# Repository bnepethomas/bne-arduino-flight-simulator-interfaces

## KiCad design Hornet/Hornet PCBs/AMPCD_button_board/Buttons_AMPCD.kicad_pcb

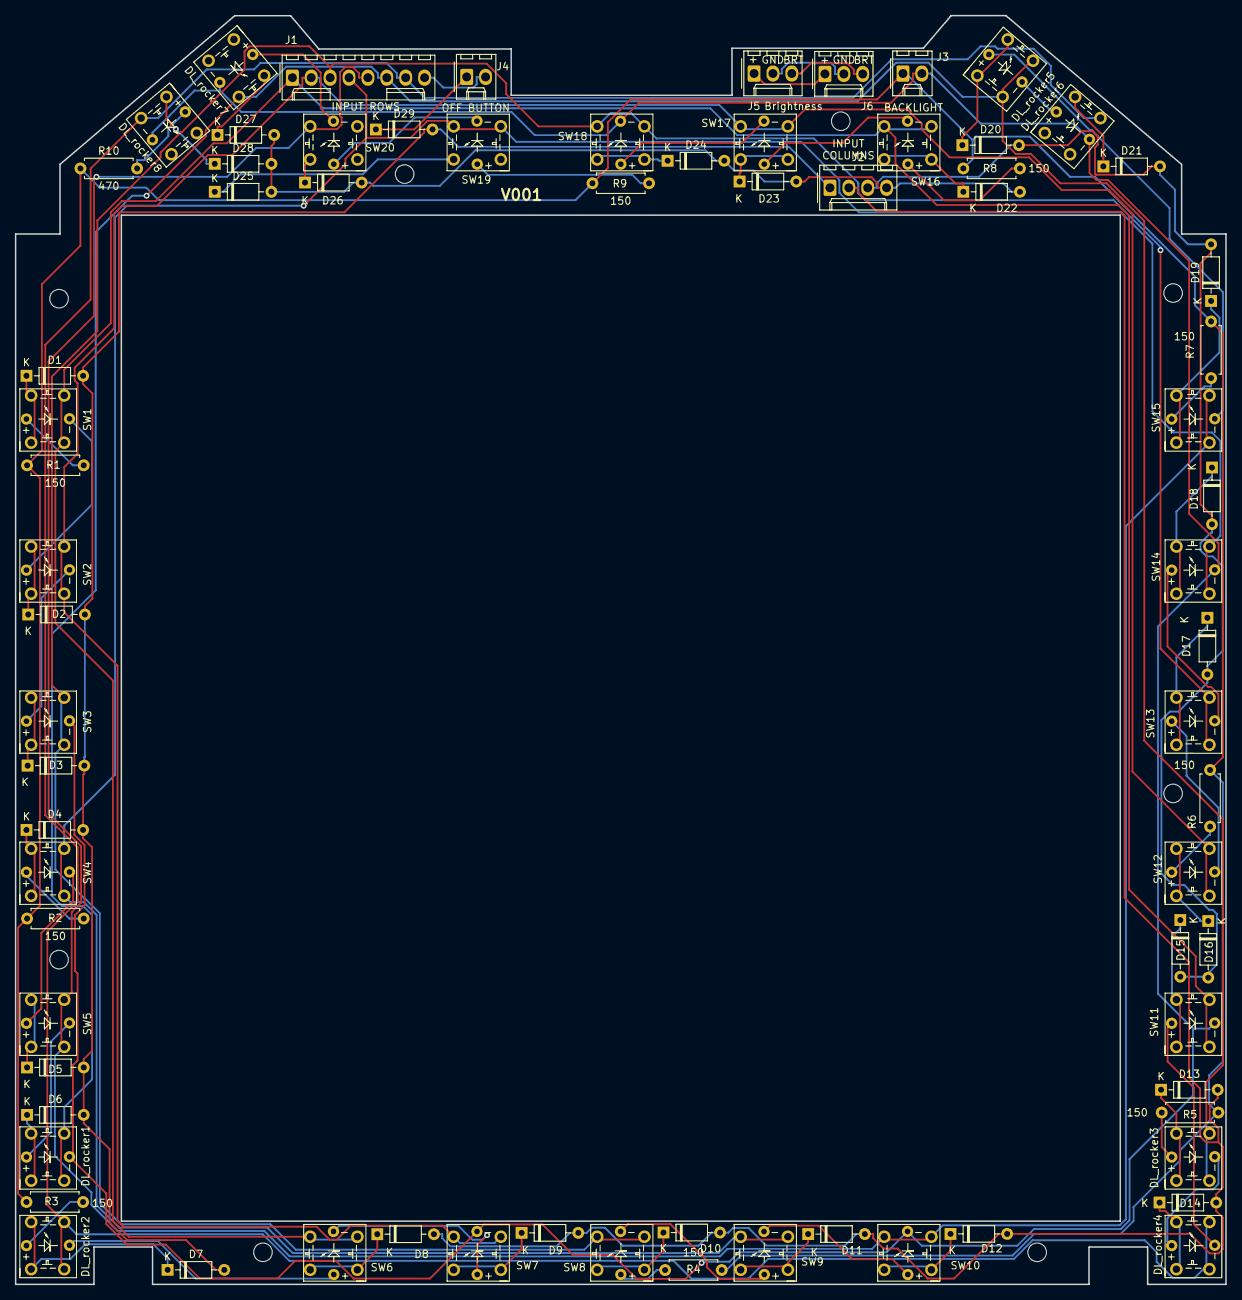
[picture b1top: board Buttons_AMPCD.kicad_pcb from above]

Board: 2 copper layers, 162.8 x 170.7 mm, 81 parts (0 on the bottom side), 74 nets.

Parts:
D1, D2, D3, D4, D5, D6, D7, D8, D9, D10, D11, D12, D13, D14, D15, D16, D17, D18, D19, D20, D21, D22, D23, D24, D25, D26, D27, D28, D29: 1N4148; D_DO-35_SOD27_P7.62mm_Horizontal
DL_rocker1, DL_rocker2, DL_rocker3, DL_rocker4, DL_rocker5, DL_rocker6, DL_rocker7, DL_rocker8: SW_Push; PT_Small_Tactile_Switch_With_LED
H1, H2, H3, H4, H5, H6, H7, H8: MountingHole; MountingHole_2.5mm
J1: Conn_01x08_Female; Molex_1x08_P2.54mm_Vertical
J2: Conn_01x04_Female; Molex_1x04_P2.54mm_Vertical
J3, J4: Conn_01x02_Female; Molex_1x02_P2.54mm_Vertical
J5, J6: Conn_01x03_Female; Molex_1x03_P2.54mm_Vertical
R1, R2, R3, R4, R5, R6, R7, R8, R9: 150; R_Axial_DIN0207_L6.3mm_D2.5mm_P7.62mm_Horizontal
R10: 470; R_Axial_DIN0207_L6.3mm_D2.5mm_P7.62mm_Horizontal
SW1, SW2, SW3, SW4, SW5, SW6, SW7, SW8, SW9, SW10, SW11, SW12, SW13, SW14, SW15, SW16, SW17, SW18, SW19, SW20: SW_Push; PT_Small_Tactile_Switch_With_LED

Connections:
/Backlight+12V: J3.1, R1.1, R2.1, R3.1, R4.1, R5.1, R6.1, R7.1, R8.1, R9.1, R10.1
/Col0: D1.2, D2.2, D3.2, D4.2, D5.2, D6.2, D7.2, D29.2, J2.1
/Col1: D8.2, D9.2, D10.2, D11.2, D12.2, D13.2, D14.2, J2.2
/Col2: D15.2, D16.2, D17.2, D18.2, D19.2, D20.2, D21.2, J2.3
/Col3: D22.2, D23.2, D24.2, D25.2, D26.2, D27.2, D28.2, J2.4
/Row0: J1.1, SW1.3, SW1.4, SW6.3, SW6.4, SW11.3, SW11.4, SW16.3, SW16.4
/Row1: J1.2, SW2.3, SW2.4, SW7.3, SW7.4, SW12.3, SW12.4, SW17.3, SW17.4
/Row2: J1.3, SW3.3, SW3.4, SW8.3, SW8.4, SW13.3, SW13.4, SW18.3, SW18.4
/Row3: J1.4, SW4.3, SW4.4, SW9.3, SW9.4, SW14.3, SW14.4, SW19.3, SW19.4
/Row4: J1.5, SW5.3, SW5.4, SW10.3, SW10.4, SW15.3, SW15.4, SW20.4
/Row5: DL_rocker1.3, DL_rocker1.4, DL_rocker3.3, DL_rocker3.4, DL_rocker5.3, DL_rocker5.4, DL_rocker7.4, J1.6
/Row6: DL_rocker2.3, DL_rocker2.4, DL_rocker4.3, DL_rocker4.4, DL_rocker6.4, DL_rocker8.3, J1.7
/Row7: J1.8, J4.2
GND: DL_rocker1.6, DL_rocker6.6, DL_rocker7.6, DL_rocker8.6, J3.2, SW3.6, SW7.6, SW10.6, SW11.6, SW14.6, SW18.6
unnamed: D1.1, SW1.1, SW1.2
unnamed: D2.1, SW2.1, SW2.2
unnamed: D3.1, SW3.1, SW3.2
unnamed: D4.1, SW4.1, SW4.2
unnamed: D5.1, SW5.1, SW5.2
unnamed: D6.1, DL_rocker1.1, DL_rocker1.2
unnamed: D7.1, DL_rocker2.1, DL_rocker2.2
unnamed: D8.1, SW6.1, SW6.2
unnamed: D9.1, SW7.1, SW7.2
unnamed: D10.1, SW8.1, SW8.2
unnamed: D11.1, SW9.1, SW9.2
unnamed: D12.1, SW10.1, SW10.2
unnamed: D13.1, DL_rocker3.1, DL_rocker3.2
unnamed: D14.1, DL_rocker4.1, DL_rocker4.2
unnamed: D15.1, SW11.1, SW11.2
unnamed: D16.1, SW12.1, SW12.2
unnamed: D17.1, SW13.1, SW13.2
unnamed: D18.1, SW14.1, SW14.2
unnamed: D19.1, SW15.1, SW15.2
unnamed: D20.1, DL_rocker5.1, DL_rocker5.2
unnamed: D21.1, DL_rocker6.2
unnamed: D22.1, SW16.1, SW16.2
unnamed: D23.1, SW17.1, SW17.2
unnamed: D24.1, SW18.1, SW18.2
unnamed: D25.1, SW19.2
unnamed: D26.1, SW20.2
unnamed: D27.1, DL_rocker7.2
unnamed: D28.1, DL_rocker8.1
unnamed: D29.1, J4.1
unnamed: DL_rocker1.5, SW5.6
unnamed: DL_rocker2.5, R3.2
unnamed: DL_rocker2.6, SW6.5
unnamed: DL_rocker3.5, R5.2
unnamed: DL_rocker3.6, DL_rocker4.5
unnamed: DL_rocker4.6, SW11.5
unnamed: DL_rocker5.5, SW15.6
unnamed: DL_rocker5.6, DL_rocker6.5
unnamed: DL_rocker7.5, SW20.6
unnamed: DL_rocker8.5, R10.2
unnamed: J5.1, J6.1
unnamed: J5.2, J6.2
unnamed: J5.3, J6.3
unnamed: R1.2, SW1.5
unnamed: R2.2, SW4.5
unnamed: R4.2, SW8.5
unnamed: R6.2, SW12.5
unnamed: R7.2, SW15.5
unnamed: R8.2, SW16.5
unnamed: R9.2, SW19.5
unnamed: SW1.6, SW2.5
unnamed: SW2.6, SW3.5
unnamed: SW4.6, SW5.5
unnamed: SW6.6, SW7.5
unnamed: SW8.6, SW9.5
unnamed: SW9.6, SW10.5
unnamed: SW12.6, SW13.5
unnamed: SW13.6, SW14.5
unnamed: SW16.6, SW17.5
unnamed: SW17.6, SW18.5
unnamed: SW19.6, SW20.5

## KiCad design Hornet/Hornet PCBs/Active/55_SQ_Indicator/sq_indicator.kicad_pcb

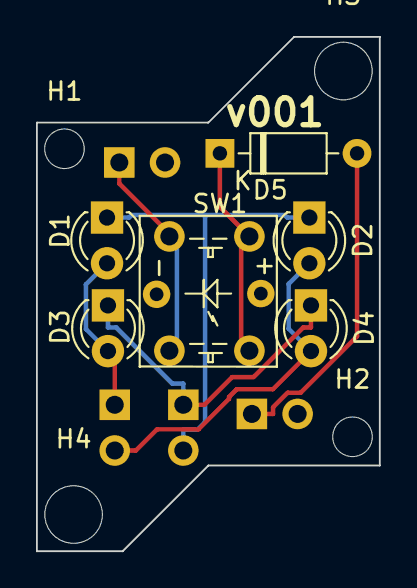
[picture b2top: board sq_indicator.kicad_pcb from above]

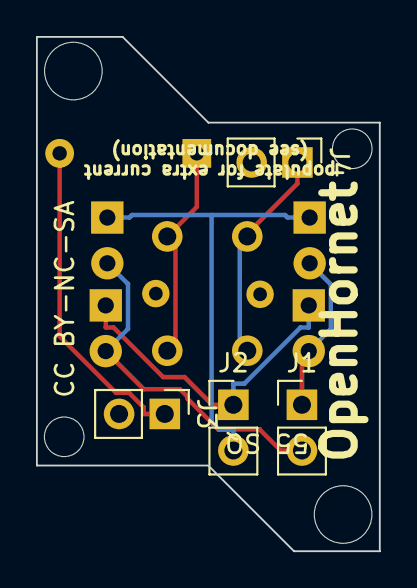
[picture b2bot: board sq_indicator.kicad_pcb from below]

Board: 2 copper layers, 19.1 x 28.6 mm, 14 parts (4 on the bottom side), 7 nets.

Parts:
D1, D2, D3, D4: LED; LED_D3.0mm
D5: 1N4148; D_DO-35_SOD27_P7.62mm_Horizontal
H1, H2: MountingHole; MountingHole_2.2mm_M2
H3, H4: MountingHole; MountingHole_3.2mm_M3
J1: LedAnode; PinHeader_1x02_P2.54mm_Vertical
J2: LedCathode; PinHeader_1x02_P2.54mm_Vertical
J3: SwitchCol; PinHeader_1x02_P2.54mm_Vertical
J4: SwitchRow; PinHeader_1x02_P2.54mm_Vertical
SW1: push; PT_Small_Tactile_Switch_With_LED

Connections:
unnamed: D1.1, D2.1, J2.2
unnamed: D1.2, D3.2, J1.1
unnamed: D2.2, D4.2, J1.2
unnamed: D3.1, D4.1, J2.1
unnamed: D5.1, SW1.1, SW1.2
unnamed: D5.2, J3.1
unnamed: J4.1, SW1.3, SW1.4

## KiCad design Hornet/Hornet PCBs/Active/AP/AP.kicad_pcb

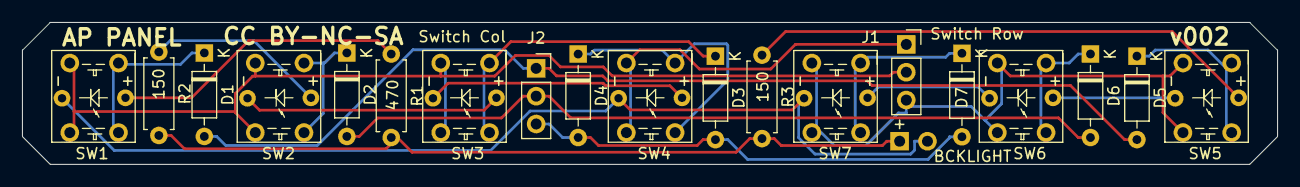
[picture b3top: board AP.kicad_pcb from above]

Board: 2 copper layers, 114.6 x 13.0 mm, 20 parts (1 on the bottom side), 22 nets.

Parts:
D1, D2, D3, D4, D5, D6, D7: D; D_Signal_P7.62mm_Horizontal
J1: ROWS; PinSocket_1x03_P2.54mm_Vertical
J2: COLS; PinSocket_1x03_P2.54mm_Vertical
J3: Conn_01x02_Female; PinSocket_1x02_P2.54mm_Vertical
R1: 470; R_Axial_DIN0207_L6.3mm_D2.5mm_P7.62mm_Horizontal
R2, R3: 150; R_Axial_DIN0207_L6.3mm_D2.5mm_P7.62mm_Horizontal
SW1, SW2, SW3, SW4, SW5, SW6, SW7: SW_SPST; PT_Small_Tactile_Switch_With_LED

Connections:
/+BCKLGT: J3.1, R1.2, R2.2, R3.2
/-BCKLGT: J3.2, SW1.6, SW4.6, SW7.6
/COL8: D1.2, D5.2, J2.1
/COL9: D2.2, D6.2, J2.2
/COL10: D3.2, D4.2, D7.2, J2.3
/ROW2: J1.1, SW4.3, SW4.4
/ROW5: J1.2, SW1.3, SW1.4, SW2.3, SW2.4, SW3.3, SW3.4
/ROW6: J1.3, SW5.3, SW5.4, SW6.3, SW6.4, SW7.3, SW7.4
unnamed: D1.1, SW1.1, SW1.2
unnamed: D2.1, SW2.1, SW2.2
unnamed: D3.1, SW3.1, SW3.2
unnamed: D4.1, SW4.1, SW4.2
unnamed: D5.1, SW5.1, SW5.2
unnamed: D6.1, SW6.1, SW6.2
unnamed: D7.1, SW7.1, SW7.2
unnamed: R1.1, SW1.5
unnamed: R2.1, SW2.5
unnamed: R3.1, SW5.5
unnamed: SW2.6, SW3.5
unnamed: SW3.6, SW4.5
unnamed: SW5.6, SW6.5
unnamed: SW6.6, SW7.5

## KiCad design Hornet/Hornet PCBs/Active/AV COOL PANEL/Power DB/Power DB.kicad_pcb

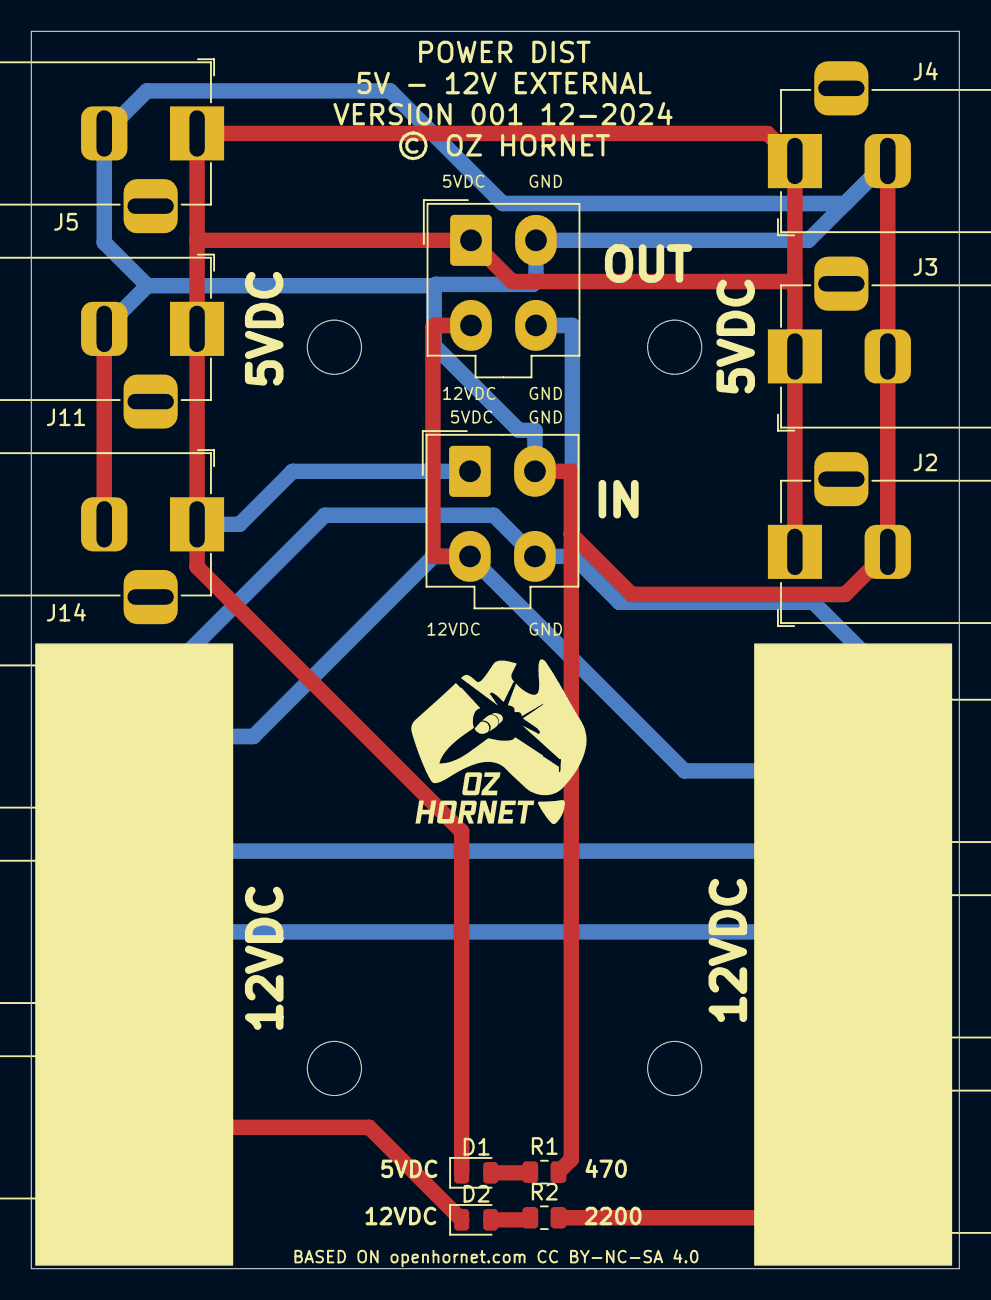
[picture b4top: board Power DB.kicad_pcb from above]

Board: 2 copper layers, 60.0 x 80.0 mm, 18 parts (0 on the bottom side), 6 nets.

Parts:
D1, D2: LED; LED_0805_2012Metric
J1, J10: Mini-Fit Jr. 2x02; Molex_Mini-Fit_Jr_5566-04A_2x02_P4.20mm_Vertical
J2, J3, J4, J5, J6, J7, J8, J9, J11, J12, J13, J14: Conn_01x02_Socket; BarrelJack_Horizontal
R1, R2: R; R_0805_2012Metric

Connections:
/5VDC: D1.1 (K), J1.1, J2.1, J3.1, J4.1, J5.1, J10.1, J11.1, J14.1
/5VGND: J1.2 (Pin_3), J2.2, J3.2, J4.2, J5.2, J10.2 (Pin_3), J11.2, J14.2, R1.2
/12VDC: D2.1 (K), J1.3 (Pin_2), J6.1, J7.1, J8.1, J9.1, J10.3 (Pin_2), J12.1, J13.1
/12VGND: J1.4, J6.2, J7.2, J8.2, J9.2, J10.4, J12.2, J13.2, R2.2
unnamed: D1.2 (A), R1.1
unnamed: D2.2 (A), R2.1

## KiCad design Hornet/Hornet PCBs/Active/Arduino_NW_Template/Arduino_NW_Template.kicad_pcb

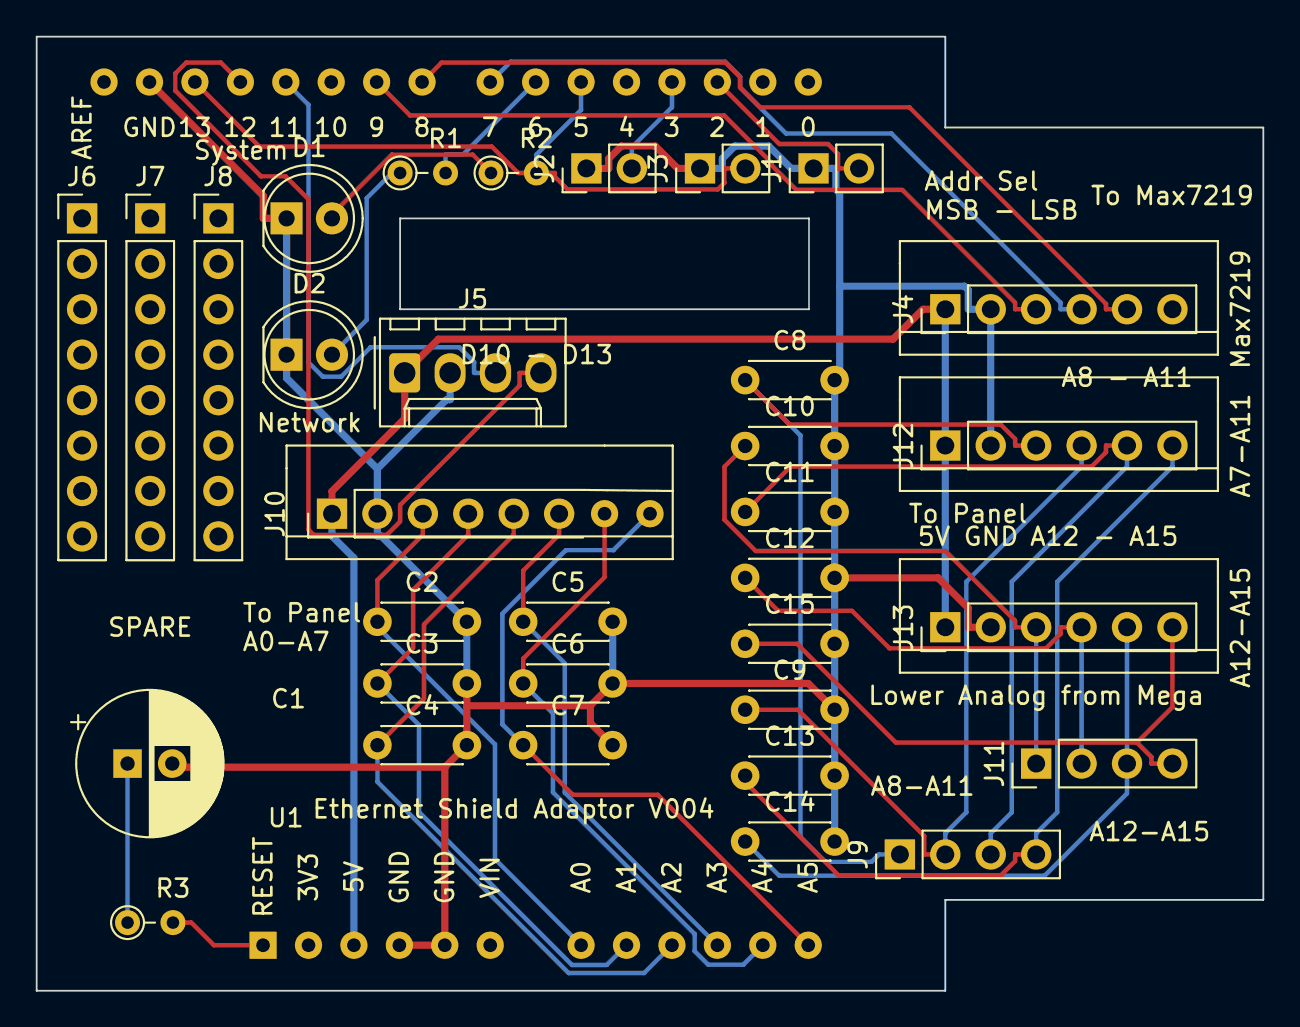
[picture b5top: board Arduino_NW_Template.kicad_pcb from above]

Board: 2 copper layers, 68.6 x 53.3 mm, 34 parts (0 on the bottom side), 29 nets.

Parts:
C1: 47uF; PT_CP_Radial_D8.0mm_P2.50mm
C2, C3, C4, C5, C6, C7, C8, C9, C10, C11, C12, C13, C14, C15: 0.1uF; C_Disc_D4.3mm_W1.9mm_P5.00mm
D1: Green; LED_D5.0mm
D2: Red; LED_D5.0mm
J1, J2, J3: Conn_01x02_Female; PinHeader_1x02_P2.54mm_Vertical
J4, J12, J13: PT_Conn_01x06; PT_PinHeader_1x06_P2.54mm_Vertical
J5: PT_Conn_01x06; Molex_1x04_P2.54mm_Vertical
J6, J7, J8: Conn_01x08_Female; PinHeader_1x08_P2.54mm_Vertical
J9, J11: Conn_01x04_Female; PinHeader_1x04_P2.54mm_Vertical
J10: Conn_01x08_Female; PT_PinHeader_1x08_P2.54mm_Vertical
R1, R2: 330; PT_R_Axial_DIN0204_L3.6mm_D1.6mm_P2.54mm_Vertical
R3: 500; PT_R_Axial_DIN0204_L3.6mm_D1.6mm_P2.54mm_Vertical
U1: PT_Ethernet_Shield; PT_Ethernet_Shield_v001

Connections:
+5V: J4.1, J5.1, J10.1, J12.1, J13.1, U1.3
GND: C1.2, C2.2, C3.2, C4.2, C5.2, C6.2, C7.2, C8.2, C9.2, C10.2, C11.2, C12.2, C13.2, C14.2, C15.2, D1.1, D2.1, J1.1, J2.1, J3.1, J4.2, J5.2, J10.2, J12.2, J13.2, U1.4, U1.5, U1.27
unnamed: C1.1, R3.1
unnamed: C2.1, J10.3, U1.7
unnamed: C3.1, J10.4, U1.8
unnamed: C4.1, J10.5, U1.9
unnamed: C5.1, J10.6, U1.10
unnamed: C6.1, J10.7, U1.11
unnamed: C7.1, J10.8, U1.12
unnamed: C8.1, J9.1, J12.3
unnamed: C9.1, J9.2, J12.4
unnamed: C10.1, J11.1, J13.3
unnamed: C11.1, J9.3, J12.5
unnamed: C12.1, J11.2, J13.4
unnamed: C13.1, J9.4, J12.6
unnamed: C14.1, J11.3, J13.5
unnamed: C15.1, J11.4, J13.6
unnamed: D1.2, R2.1
unnamed: D2.2, R1.1
unnamed: J1.2, U1.15
unnamed: J2.2, U1.16
unnamed: J3.2, R2.2, U1.18, U1.26
unnamed: J4.3, U1.22
unnamed: J4.4, U1.20
unnamed: J4.5, U1.21
unnamed: J5.3, U1.24
unnamed: J5.4, U1.25
unnamed: R1.2, U1.19
unnamed: R3.2, U1.1

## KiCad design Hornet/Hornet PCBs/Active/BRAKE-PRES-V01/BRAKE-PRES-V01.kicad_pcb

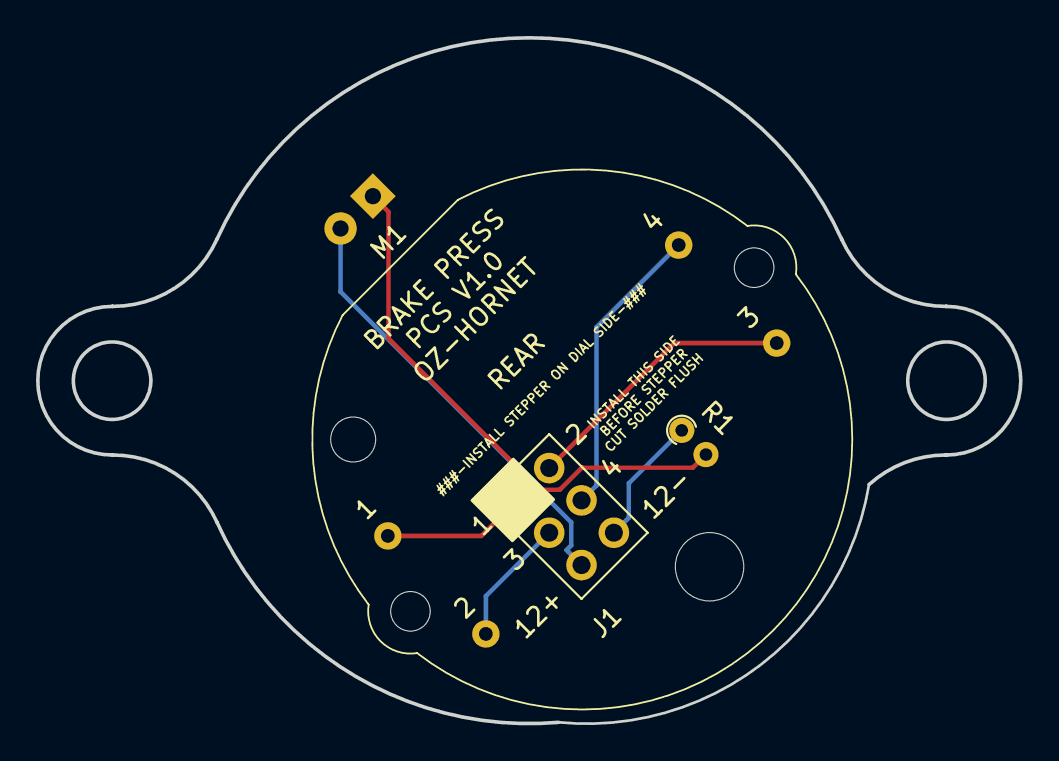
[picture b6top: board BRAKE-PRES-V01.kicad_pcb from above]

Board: 2 copper layers, 54.6 x 38.1 mm, 4 parts (1 on the bottom side), 7 nets.

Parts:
D1: LED; LED_D3.0mm_Clear
J1: Conn_02x03_Odd_Even; PinHeader_2x03_P2.54mm_Vertical
M1: Stepper_Motor_bipolar; VID29-02
R1: R; R_Axial_DIN0204_L3.6mm_D1.6mm_P1.90mm_Vertical

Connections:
/LED+12V: D1.2 (A), J1.5
/LED-12V: J1.6, R1.1
/STEPPER-1-1: J1.1, M1.1
/STEPPER-1-2: J1.3, M1.2 (-)
/STEPPER-1-3: J1.2, M1.3
/STEPPER-1-4: J1.4, M1.4
unnamed: D1.1 (K), R1.2

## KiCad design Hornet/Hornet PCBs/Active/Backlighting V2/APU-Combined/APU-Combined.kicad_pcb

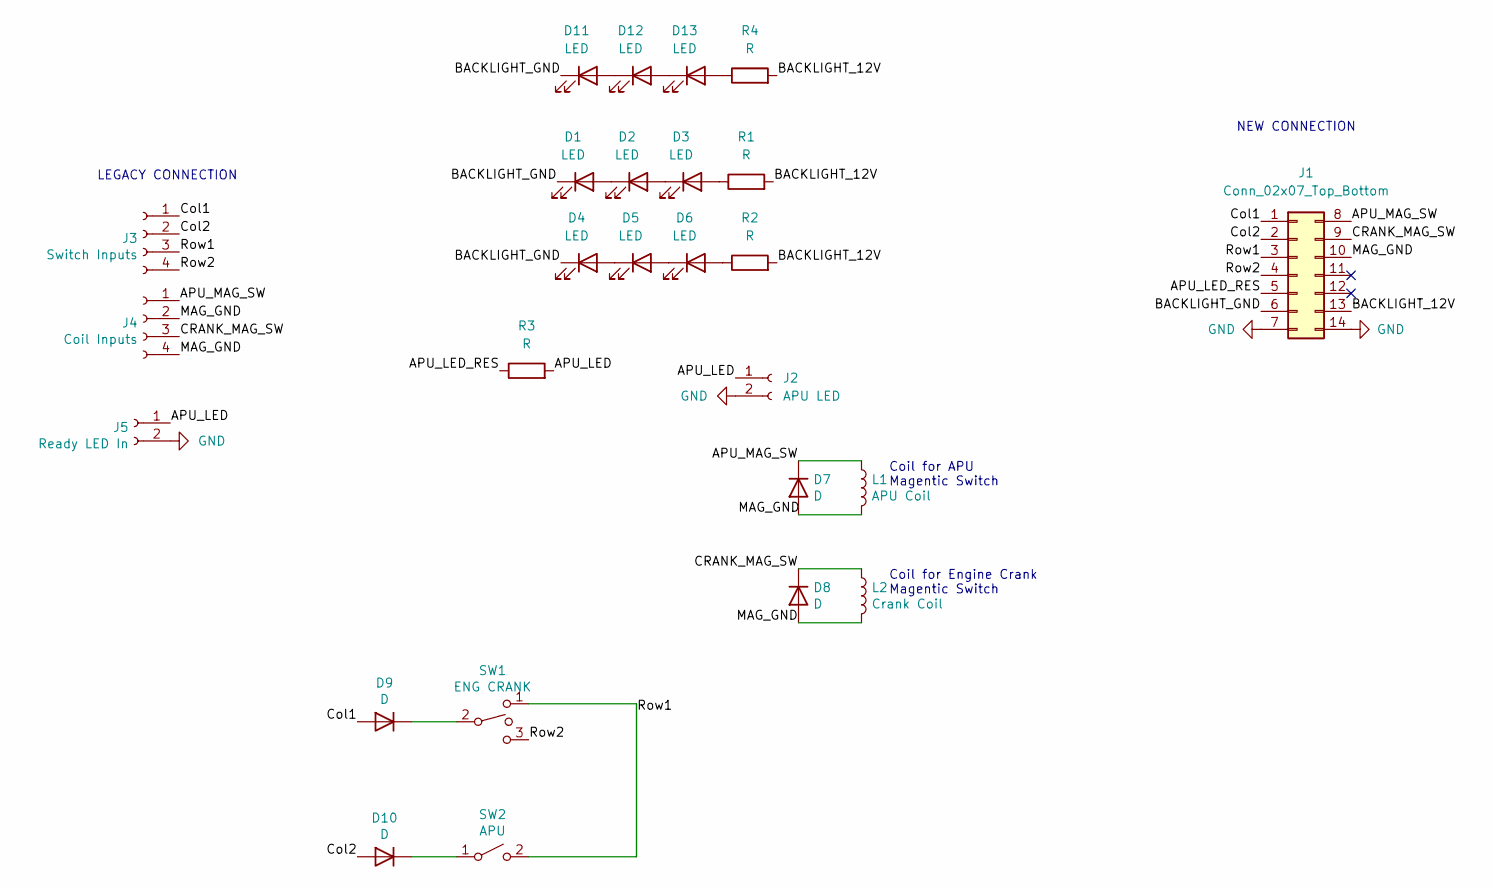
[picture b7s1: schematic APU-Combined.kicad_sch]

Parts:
D1, D2, D3, D4, D5, D6, D11, D12, D13: LED; LED_D3.0mm_FlatTop
D7, D8: D; D_DO-41_SOD81_P7.62mm_Horizontal
D9, D10: D; D_DO-34_SOD68_P7.62mm_Horizontal
J1: Conn_02x07_Top_Bottom; PinHeader_2x07_P2.54mm_Vertical
J2: APU LED; Molex_KK-254_AE-6410-02A_1x02_P2.54mm_Vertical
J3: Switch Inputs; Molex_KK-254_AE-6410-04A_1x04_P2.54mm_Vertical
J4: Coil Inputs; Molex_KK-254_AE-6410-04A_1x04_P2.54mm_Vertical
J5: Ready LED In; Molex_KK-254_AE-6410-02A_1x02_P2.54mm_Vertical
L1: APU Coil; Molex_KK-254_AE-6410-02A_1x02_P2.54mm_Vertical
L2: Crank Coil; Molex_KK-254_AE-6410-02A_1x02_P2.54mm_Vertical
R1, R2, R3, R4: R; R_Axial_DIN0204_L3.6mm_D1.6mm_P7.62mm_Horizontal
SW1: ENG CRANK; Molex_KK-254_AE-6410-03A_1x03_P2.54mm_Vertical
SW2: APU; Molex_KK-254_AE-6410-02A_1x02_P2.54mm_Vertical

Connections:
/APU_LED: J2.1, J5.1, R3.2
/APU_LED_RES: J1.5, R3.1
/APU_MAG_SW: D7.1 (K), J1.8, J4.1, L1.1
/BACKLIGHT_12V: J1.13, R1.2, R2.2, R4.2
/BACKLIGHT_GND: D1.1 (K), D4.1 (K), D11.1 (K), J1.6
/CRANK_MAG_SW: D8.1 (K), J1.9, J4.3, L2.1
/Col1: D9.2 (A), J1.1, J3.1
/Col2: D10.2 (A), J1.2, J3.2
/MAG_GND: D7.2 (A), D8.2 (A), J1.10, J4.2, J4.4, L1.2, L2.2
/Row1: J1.3, J3.3, SW1.1, SW2.2 (B)
/Row2: J1.4, J3.4, SW1.3
GND: J1.7, J1.14, J2.2, J5.2
unnamed: D1.2 (A), D2.1 (K)
unnamed: D2.2 (A), D3.1 (K)
unnamed: D3.2 (A), R1.1
unnamed: D4.2 (A), D5.1 (K)
unnamed: D5.2 (A), D6.1 (K)
unnamed: D6.2 (A), R2.1
unnamed: D9.1 (K), SW1.2
unnamed: D10.1 (K), SW2.1 (A)
unnamed: D11.2 (A), D12.1 (K)
unnamed: D12.2 (A), D13.1 (K)
unnamed: D13.2 (A), R4.1

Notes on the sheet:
NEW CONNECTION
Coil for Engine Crank Magentic Switch
LEGACY CONNECTION
Coil for APU Magentic Switch

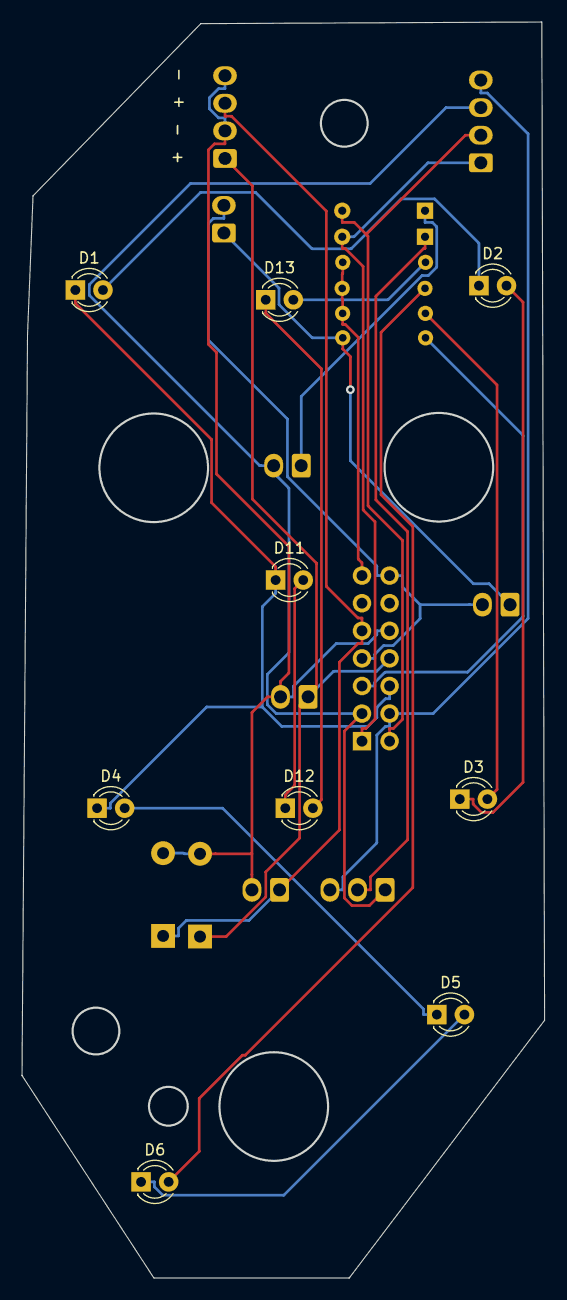
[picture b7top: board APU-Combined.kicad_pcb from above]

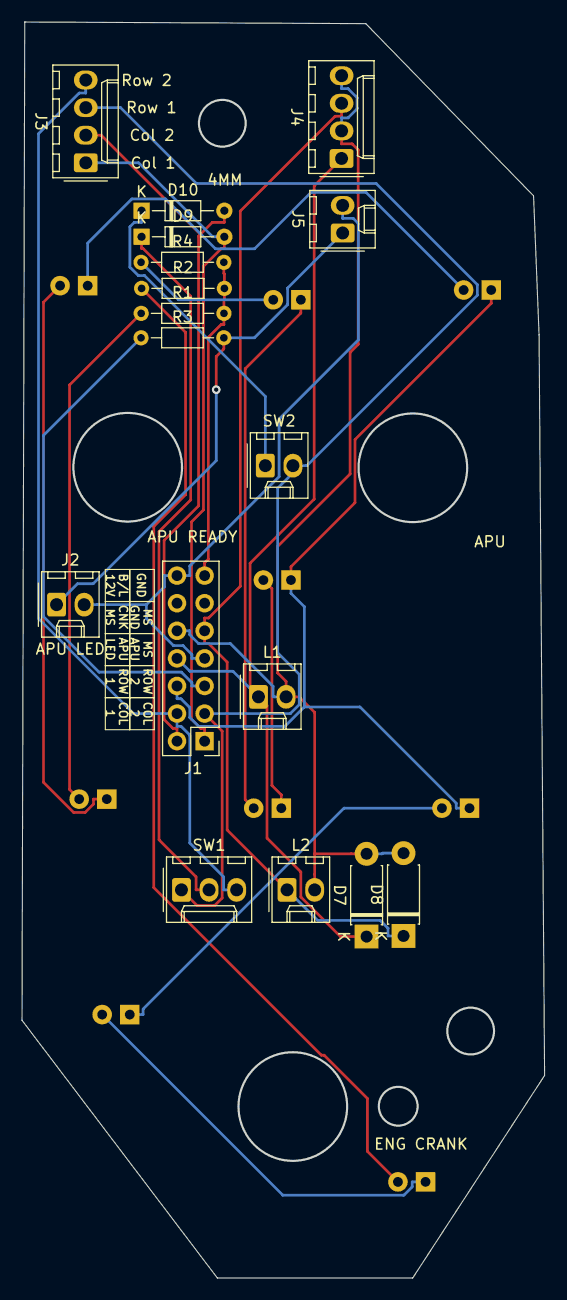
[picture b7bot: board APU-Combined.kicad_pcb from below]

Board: 2 copper layers, 48.1 x 115.6 mm, 26 parts (17 on the bottom side), 23 nets.

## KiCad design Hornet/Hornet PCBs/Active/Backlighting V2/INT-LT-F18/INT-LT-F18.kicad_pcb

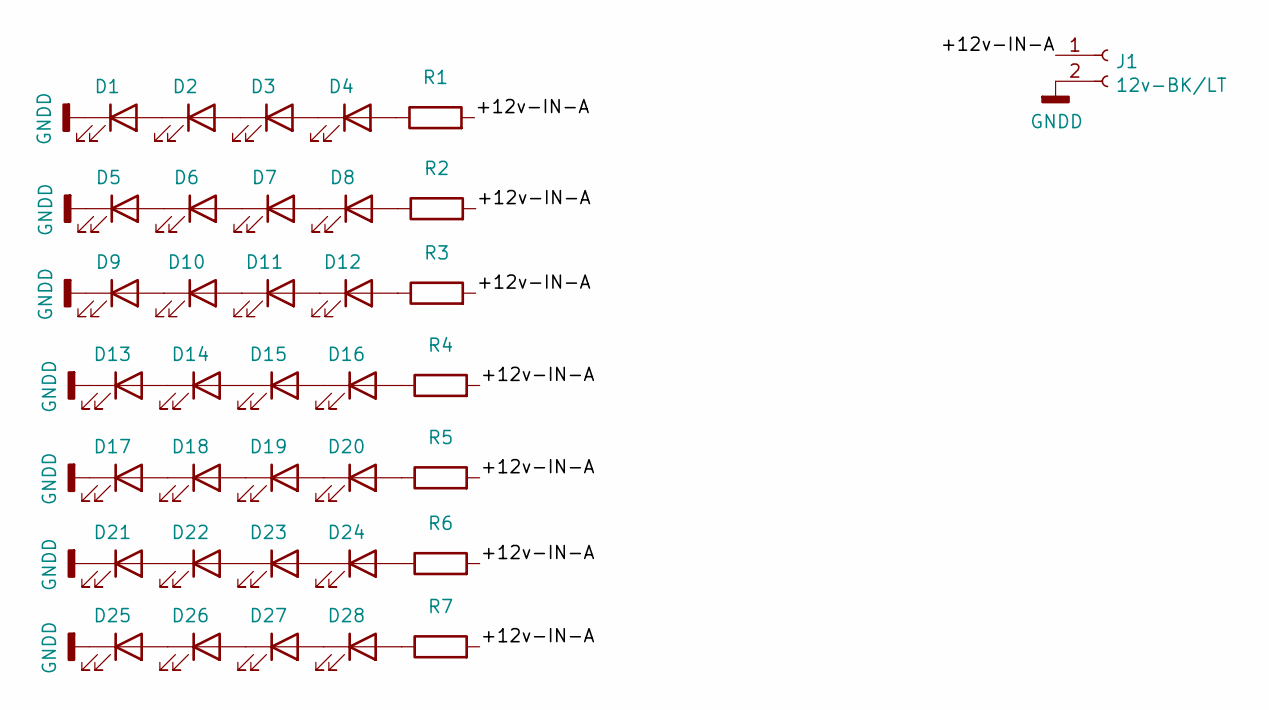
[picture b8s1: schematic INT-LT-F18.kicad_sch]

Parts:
D1, D2, D3, D4, D5, D6, D7, D8, D9, D10, D11, D12, D13, D14, D15, D16, D17, D18, D19, D20, D21, D22, D23, D24, D25, D26, D27, D28: LED; LED_HL-A-3528U51GC-S1-13HL
J1: 12v-BK/LT; Molex_KK-254_AE-6410-02A_1x02_P2.54mm_Vertical
R1, R2, R3, R4, R5, R6, R7: 180; R_0402_1005Metric

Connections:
/+12v-IN-A: J1.1, R1.2, R2.2, R3.2, R4.2, R5.2, R6.2, R7.2
GNDD: D1.1 (K), D5.1 (K), D9.1 (K), D13.1 (K), D17.1 (K), D21.1 (K), D25.1 (K), J1.2
unnamed: D1.2 (A), D2.1 (K)
unnamed: D2.2 (A), D3.1 (K)
unnamed: D3.2 (A), D4.1 (K)
unnamed: D4.2 (A), R1.1
unnamed: D5.2 (A), D6.1 (K)
unnamed: D6.2 (A), D7.1 (K)
unnamed: D7.2 (A), D8.1 (K)
unnamed: D8.2 (A), R2.1
unnamed: D10.2 (A), D11.1 (K)
unnamed: D9.2 (A), D10.1 (K)
unnamed: D11.2 (A), D12.1 (K)
unnamed: D12.2 (A), R3.1
unnamed: D13.2 (A), D14.1 (K)
unnamed: D14.2 (A), D15.1 (K)
unnamed: D15.2 (A), D16.1 (K)
unnamed: D16.2 (A), R4.1
unnamed: D17.2 (A), D18.1 (K)
unnamed: D18.2 (A), D19.1 (K)
unnamed: D19.2 (A), D20.1 (K)
unnamed: D20.2 (A), R5.1
unnamed: D21.2 (A), D22.1 (K)
unnamed: D22.2 (A), D23.1 (K)
unnamed: D23.2 (A), D24.1 (K)
unnamed: D24.2 (A), R6.1
unnamed: D25.2 (A), D26.1 (K)
unnamed: D26.2 (A), D27.1 (K)
unnamed: D27.2 (A), D28.1 (K)
unnamed: D28.2 (A), R7.1

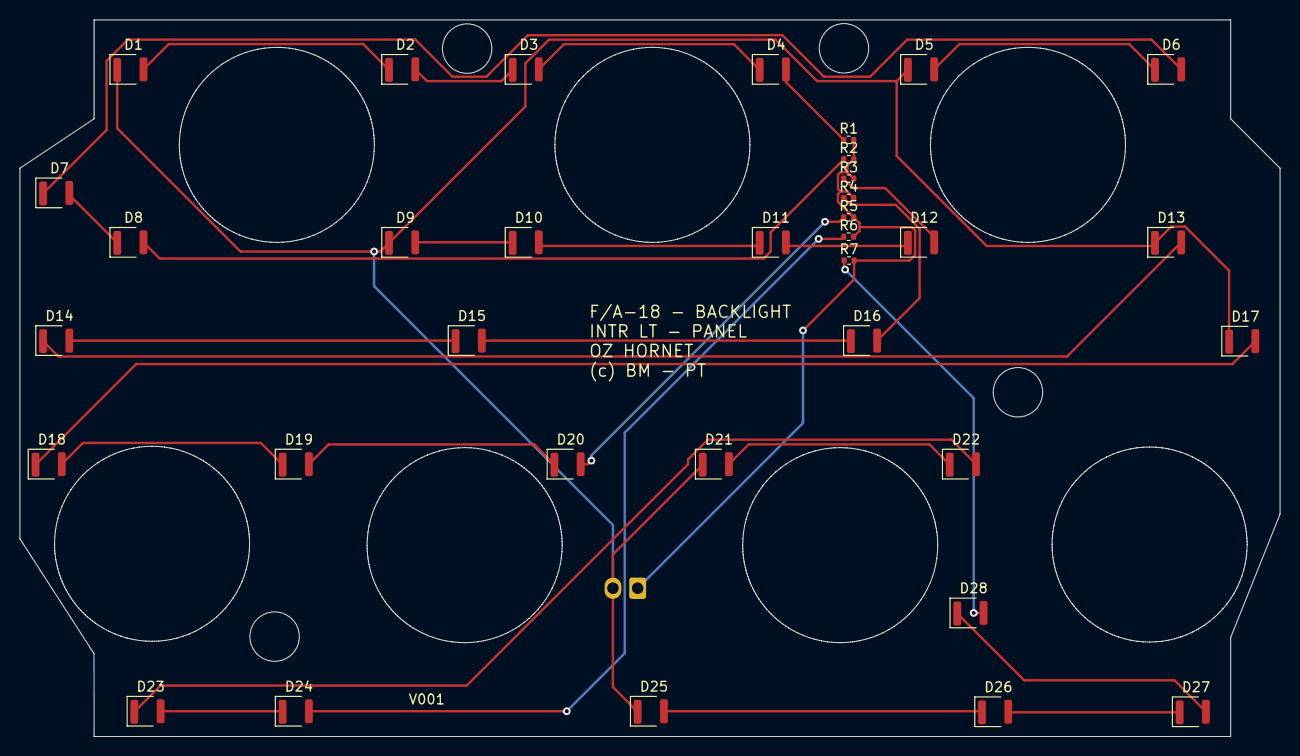
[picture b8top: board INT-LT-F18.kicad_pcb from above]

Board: 2 copper layers, 129.5 x 73.7 mm, 36 parts (1 on the bottom side), 30 nets.

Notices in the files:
Hornet/Hornet PCBs/Active/55_SQ_Indicator/sq_indicator.kicad_pcb:
CC BY-NC-SA
Hornet/Hornet PCBs/Active/AV COOL PANEL/Power DB/Power DB.kicad_pcb:
© OZ HORNET
BASED ON openhornet.com CC BY-NC-SA 4.0
